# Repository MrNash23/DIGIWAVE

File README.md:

<h3 align="center">A pocket terminal for digital radio modes</h3>

<p align="center">
  Firmware for the <a href="https://lilygo.cc/products/t-lora-pager">LilyGo T-LoRa Pager</a>:
  FT8, FT4, CW, RTTY, NAVTEX, WEFAX and SSTV on a device that fits in a jacket pocket,
  and a scanner that tells them apart.
</p>

## What it does

DIGIWAVE listens to the audio of a radio, decodes what it hears and shows it on
the pager's display. In the modes that can transmit it also generates the audio
and keys the radio. No computer is involved.

<table>
  <tr>
    <td align="center"><br><b>FT8</b></td>
    <td align="center"><br><b>FT4</b></td>
    <td align="center"><br><b>CW</b></td>
    <td align="center"><br><b>RTTY</b></td>
    <td align="center"><br><b>NAVTEX</b></td>
    <td align="center"><br><b>WEFAX</b></td>
    <td align="center"><br><b>SSTV</b></td>
    <td align="center"><br><b>SCAN</b></td>
  </tr>
</table>

| Mode | Receive | Transmit |
| --- | --- | --- |
| FT8, FT4 | yes, with locator and country of each station | yes, with automatic QSO sequence and ADIF log |
| CW | yes, in a 100 Hz window that is moved with the wheel | yes, from the keyboard |
| RTTY (45.45 / 50 baud) | yes | yes |
| NAVTEX | yes | - |
| WEFAX (120 LPM) | yes, saved as BMP on the SD card | - |
| SSTV (Martin 1/2, Scottie 1/2, Robot 36, PD 120/180) | yes, in colour, saved as BMP on the SD card | - |
| Mode scanner (experimental) | names the mode of a signal: FT8, FT4, CW, RTTY, NAVTEX, PSK31/63, SSTV, WEFAX | - |

### Features

- **Mode scanner** (experimental): the SCAN tile listens to the strongest
  signal, or to the one picked with the wheel, and names its mode from its
  width, tones, symbol rate and length of transmission, with the measured
  shift, baud rate or speed. Enter opens the mode that decodes it and takes the
  tones over, for instance mark, shift and speed of an RTTY station
- **Waterfall** under the decodes in FT8, FT4, CW, RTTY and NAVTEX
- **Full FT8/FT4 contacts**: call CQ or answer a station with one press; the
  sequence runs by itself and the contact is written to an ADIF logbook on the SD card
- **Worked before**: stations already in the logbook of the device are greyed
  out in the list, on this band or only on another one
- **CQ with an addition** (POTA, SOTA, DX, QRP ...), **distance** to every
  station heard, and **figures over the logbook**: QSOs per band and mode,
  countries, farthest contact
- **Weather by RTTY**: the frequencies of the German weather service DWD are in
  the RTTY list; choosing one sets speed and shift
- **CB (11 m) operation** for FT8 and FT4: CB callsigns such as `26AT016`, the
  message sequence of WSJT-CB and the country list by division number
- **The own contact at a glance**: what is sent appears in the list with what
  is heard, and while calling or working a station the list shows just that
  contact (key V switches between it and everything heard)
- **A free spot to transmit**: the spectrum of the last half minute shows
  where the band is quiet; key G moves the TX frequency there, key F tunes it
  with the wheel on the waterfall, and key E chooses the first or the second
  slots for calling CQ
- **Voice announcements** (optional): a new station calling CQ, a station
  calling you, a QSO started and logged, spoken through the pager's speaker
- **Band and frequency for the logbook**: the radio is tuned by hand, so key B
  in FT8 and FT4 opens the list of the usual frequencies per band (or takes a
  typed one). FT8, FT4 and CB operation each remember their own
- **Exact time from GPS** with the pulse-per-second signal. Without reception
  the phone page sets the clock from the phone's time, measured like NTP, and
  the real-time clock keeps it in between
- **Locator from GPS**, or entered by hand
- **Phone page over Wi-Fi** (switched on and off in the setup): the pager opens its own access point and serves a
  page with the decodes, the main controls, received WEFAX pictures and the
  logbook download. In the logbook, key Q shows QR codes that join the Wi-Fi
  and fetch the ADIF file
- **Home network**: set up from the phone without typing on the pager. Setup >
  Home Wi-Fi shows a code that joins the pager and one that opens a page
  listing the networks in reach, where the password is pasted. The pager then
  joins that network besides its own access point whenever its Wi-Fi is on,
  and answers there as `digiwave.local`, so a logging program at home can take
  the logbook over and send its own QSOs back (see
  [Logbook over the home network](#logbook-over-the-home-network)). With Wi-Fi
  off, the home network is left alone too
- **Worked from home**: QSOs a logging program puts on the card mark those
  stations as worked in the list of decodes, and key A in the logbook shows them
  together with the own QSOs, with their distance
- **Broadcast plans** of the German weather service DWD for WEFAX and RTTY: the
  menu names the next broadcast and the plan counts down to it; the plans can
  be edited on the phone page
- **Battery** charge in the corner of the screen, from the fuel gauge checked
  against the voltage curve of the cell
- **Power saving**: the display goes off after three minutes without input, and
  the device goes to sleep when nothing is received either. Pressing the wheel
  wakes it. "Switch off" is in the setup

## Hardware: connecting a radio

<table>
  <tr>
    <td width="40%"></td>
    <td width="30%"></td>
    <td width="30%"></td>
  </tr>
</table>

A small interface board plugs into the pager's 12-pin port. It carries its own
ES8311 audio codec with line in, line out and a PTT output, and connects to
the radio with one TRRS cable wired like the Digirig. The firmware uses it
whenever it is plugged in (Setup, "Audio"); receive and transmit levels are set
in the setup and with the two trimmers, which can be reached through the lid of
its 3D-printed case.

Schematic, KiCad project, Gerber files with parts list, 3D views and the STL
files of the case are in [`hardware`](hardware), described on its own
[page](hardware/README.md).

Without the board, audio goes through the built-in microphone and speaker of
the pager, so reception works held next to the speaker of any receiver.

## Status

Work in progress.

- The signal processing of all modes and the mode scanner are covered by 58
  host tests.
- On the device, FT8 reception has been checked against real signals; a slot is
  decoded in about 0.7 s.
- NAVTEX and SSTV have only been tested against generated signals; WEFAX has
  received real weather charts.
- The mode scanner is tested against generated signals down to 0 dB SNR and has
  named real RTTY of the German weather service (50 baud, 450 Hz shift).
- Transmitting works through the interface board: PTT keys the radio and FT8
  calls have gone out on the air.

## Installing

DIGIWAVE is installed as one application next to others (for example Meshtastic)
with the [Launcher](https://github.com/bmorcelli/Launcher) by bmorcelli: build
the firmware, copy `.pio/build/pager/firmware.bin` to the SD card and install it
from the Launcher. An update can also be written over USB straight into the
Launcher slot of DIGIWAVE (`ft8pag`), at the offset its partition table gives
it. The Launcher rewrites the table when applications are installed, so read it
first (`esptool.py read_flash 0x8000 0xc00 table.bin`); with the present table
the offset is 0x1a0000:

    esptool.py write_flash 0x1a0000 .pio/build/pager/firmware.bin

Do not use `pio run -t upload` on a pager with the Launcher: it writes
`partitions.csv`, the layout for running DIGIWAVE alone, together with its own
bootloader, and so removes the Launcher and the other applications.

## Building

PlatformIO with the pioarduino platform (Arduino-ESP32 3.3):

    pio run -e pager        # firmware
    pio test -e native      # host tests of the signal processing

Artwork in `DIGIWAVE_Firmware_Grafiken` is converted with `python3 tools/make_assets.py`,
the voice announcements are spoken by [Piper](https://github.com/OHF-Voice/piper1-gpl)
with `tools/make_voice.py` (setup in the script).

## Operating

The same everywhere:

| | |
| --- | --- |
| Wheel | select or tune: a tile, a station, the CW receive window, the RTTY tones |
| Wheel press | in the menu: open. In a mode: the list of its functions, with the keys that do the same directly |
| Enter | the main action of the mode: call the selected station, send the typed line, save the received picture |
| Backspace | one step back: typed text first, then the open list or page, then from the mode to the menu |
| Space + key | digits and symbols |

FT8 and FT4 keep a line with their keys at the bottom of the screen; the other
modes use the whole screen for text, spectrum or picture.

The scanner analyses every two seconds: the wheel picks a signal on the
waterfall, A goes back to the strongest, Enter opens the mode that decodes it.
A guess shows once two analyses agree. "Input too quiet" means next to no audio
arrives: check the cable and the level of the radio.

Every WEFAX line is kept in memory (half an hour of reception), so a picture
can be saved as a whole at any time, and is saved by itself when the station's
stop tone ends it. Saved pictures can be looked at on the pager
(WEFAX functions, "Saved pictures") and are shown, downloaded and deleted on
the phone page.

## Logbook over the home network

With a home network set up (Setup > Home Wi-Fi) and Wi-Fi on, the pager answers
at `http://digiwave.local`. A logging program on a computer in that network can
use three requests to keep its log and the pager's in step, in both directions:

| Request | |
| --- | --- |
| `GET /api/log` | `{"device":"DIGIWAVE", "call":"...", "qsos":12, "size":975, "station":14759, "stationqsos":92}`: QSOs and size in bytes of the pager's logbook, size of the station file and the QSOs in it; a size is `-1` while there is no such file |
| `GET /log.adi` | the pager's logbook as ADIF |
| `POST /api/station` | replaces the station file with the body (`Content-Type: text/plain`), which is written to the card as it arrives; answers `200` once it is in place |

**Taking the logbook over.** The pager only ever appends to its logbook and
never deletes from it, so it is enough to ask `/api/log` now and then and to
fetch `/log.adi` when `size` changed. Records may come again: match them on
your side, by call, date, time, band and mode. The file starts with a header
naming `DIGIWAVE` as `programid`, and every record carries `station_callsign`
and `my_gridsquare` of where it was worked, which is useful for portable
operation.

**Sending QSOs to the pager.** QSOs made elsewhere, at the home station for
instance, go into the station file. The pager marks these stations as worked in
the list of decodes and for the voice announcements, lists them in grey in the
logbook (key A) with their distance, leaves them out of the figures and never
returns them in `/log.adi`. The file is ADIF with these rules:

- one record to a line, ending in `<eor>`, lines up to 400 bytes
- oldest first: the pager keeps the newest 200 for its list
- fields read: `call` and `band` (for marking as worked), `gridsquare` and
  `my_gridsquare` (for the distance), `qso_date`, `time_on`, `mode`,
  `submode`, `rst_sent`, `rst_rcvd`
- at most 6000 records together with the pager's own logbook; the file is read
  at every start, so keep it smaller where you can. With more QSOs than that,
  send the newest of every call and band first
- send it only when it changed: compare `station` in `/api/log` with the size
  of what you sent last, which also catches another card in the pager

**Staying awake.** Each `/api/log` or `/log.adi` keeps the pager from going to
sleep for three minutes, so asking once a minute keeps it on while it is at
home. The display still goes off.

**Name and safety.** The pager announces its name over mDNS with an IPv4
address only. Resolve `digiwave.local` for IPv4: a lookup for any address
family can wait several seconds for an IPv6 answer that never comes (macOS
waits five). The interface has no password; everything in the home network can
reach it, the phone page with its transmit controls included.

## Layout of the repository

- `lib/ft8core` - hardware-independent decoders, encoders and QSO logic
- `lib/ft8_lib` - vendored [kgoba/ft8_lib](https://github.com/kgoba/ft8_lib) (MIT)
- `src` - firmware: audio and PTT interfaces, engine, user interface, web interface
- `test` - host tests and reference recordings from ft8_lib
- `hardware` - interface board (KiCad project, schematic, fabrication files) and printed case
- `PROJEKT.md` - description of the project in German

## Licence and credits

Copyright (C) 2026 Andres Leroi

DIGIWAVE is free software: you can redistribute it and/or modify it under the
terms of the GNU General Public License as published by the Free Software
Foundation, either version 3 of the License, or (at your option) any later
version. It comes without any warranty. The text is in [`LICENSE`](LICENSE).

The hardware in [`hardware`](hardware), interface board and case, is licensed
under the CERN Open Hardware Licence Version 2 - Strongly Reciprocal
(CERN-OHL-S-2.0), text in [`hardware/LICENSE`](hardware/LICENSE).

It stands on the work of others:

- **FT8 and FT4** are protocols by Joe Taylor K1JT and Steve Franke K9AN;
  coding and decoding come from [ft8_lib](https://github.com/kgoba/ft8_lib) by
  Kārlis Goba (MIT)
- **CB operation** follows [WSJT-CB](https://github.com/vash909/WSJT-CB), from
  which the list of 11 m divisions is taken (GPL-3.0)
- **The voice announcements** are spoken by Piper (GPL-3.0) with the voice
  ljspeech, trained on the public-domain LJ Speech dataset
- **The device** is driven through [LilyGoLib](https://github.com/Xinyuan-LilyGO/LilyGoLib)
  (MIT), the display through [LVGL](https://github.com/lvgl/lvgl) (MIT) with
  the Montserrat typeface (SIL Open Font License)
- **The platform** is the Arduino core for ESP32 (LGPL-2.1) on ESP-IDF (Apache-2.0)

The complete list with versions, authors and licences is in
[`THIRD-PARTY-NOTICES.md`](THIRD-PARTY-NOTICES.md). The same credits are shown
on the device under Setup, "About DIGIWAVE".

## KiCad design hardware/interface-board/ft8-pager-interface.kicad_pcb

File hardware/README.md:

<h3 align="center">DIGIWAVE interface board</h3>

<p align="center">
  Line in, line out and PTT for the LilyGo T-LoRa Pager, in a small case that
  plugs into the pager's 12-pin port. One TRRS cable goes to the radio.
</p>

## What it does

The pager has no audio connection for a radio. The board adds one: its own
ES8311 audio codec, clocked and fed over I²S from the 12-pin port, a 3.5 mm
TRRS jack for the radio and an open-collector PTT output. DIGIWAVE finds the
board at start-up and uses it instead of the built-in microphone and speaker
(Setup, "Audio").

<table>
  <tr>
    <td width="50%"></td>
    <td width="50%"></td>
  </tr>
  <tr>
    <td align="center">The assembled board</td>
    <td align="center">The same board in KiCad's 3D view</td>
  </tr>
</table>

- **Audio codec** ES8311 at I²C address 0x19 (the pager's own codec is at 0x18).
  It has no MCLK and derives its clock from BCLK.
- **One data line for both directions**: the port offers a single pin for audio
  data, so an analogue switch (SN74LVC1G3157) connects it to the codec's ADC
  while receiving and to its DAC while the PTT line is set
- **Receive**: tip of the jack → protection → trimmer RV1 → codec input
- **Transmit**: codec output → trimmer RV2 → 470 Ω → ring of the jack
- **PTT**: MMBT3904 as open collector, protected up to 15 V
- **Protection** on every line to the radio with TVS diodes
- **Supply** from the pager's 3.3 V; analogue supply through a ferrite bead,
  analogue and digital ground joined at one point

## Schematic

<p align="center">
  
</p>

The schematic as [PDF](interface-board/schematic.pdf); the KiCad 10 project is in
[`interface-board`](interface-board).

## Connections

### Pager port J3 (2 × 6, 2.54 mm)

| Pin | Signal | Use on the board |
| --- | --- | --- |
| 1 | GND | ground |
| 2 | 3V3 | supply |
| 3 | GPIO43 | I²S BCLK |
| 4 | GPIO44 | I²S LRCK |
| 8 | GPIO9 | I²S data, both directions |
| 9 | SDA | I²C to the codec |
| 10 | XL9555 P11 | PTT_CTRL: keys the radio and switches the data line to the DAC |
| 11 | SCL | I²C to the codec |
| 5, 6, 7, 12 | SPI, VBUS | not used |

### Radio jack J2 (3.5 mm TRRS)

The jack is wired like the [Digirig](https://digirig.net/), so the cables made
for it fit:

| Contact | Signal |
| --- | --- |
| Tip | audio from the radio (RX) |
| Ring 1 | audio to the radio (TX) |
| Ring 2 | PTT |
| Sleeve | ground |

### Jumpers, trimmers and test points

| Part | Purpose |
| --- | --- |
| JP2, JP3 | Ring swap. As delivered (1–2 bridged), ring 1 carries TX audio and ring 2 the PTT. Bridging 2–3 on both swaps them |
| JP1 | open: TX audio through a capacitor. Bridged: DC-coupled, for radios that need it |
| RV1 | receive level |
| RV2 | transmit level. If PTT keys the radio but nothing is heard, turn this up first |
| TP1–TP15 | BCLK, LRCK, DATA, ASDOUT, DSDIN, MCLK, SDA, SCL, 3V3, 3V3A, GND, TIP_RX, RING1, RING2, PTT_CTRL |

## Case

<table>
  <tr>
    <td width="50%"></td>
    <td width="50%"></td>
  </tr>
  <tr>
    <td align="center">Base, board and lid</td>
    <td align="center">From below: the header goes into the pager</td>
  </tr>
</table>

Two printed parts, 45.4 × 30.4 mm, 10.5 mm high when closed. The 12-pin
header comes out through the window in the base and plugs straight into the
pager. The lid has openings over both trimmers, so the levels can be set with
the case closed. The jack is reached from the side.

GitHub shows STL files as a 3D model that can be turned with the mouse:

- [`case/case-base.stl`](case/case-base.stl), base
- [`case/case-lid.stl`](case/case-lid.stl), lid
- [`interface-board/interface-board.stl`](interface-board/interface-board.stl), the assembled board

## Building one

The board was made and assembled by JLCPCB. Everything needed for the order is
in [`interface-board/fabrication`](interface-board/fabrication):

| File | Content |
| --- | --- |
| `gerber.zip` | Gerber and drill files, two layers |
| `bom-jlcpcb.csv` | parts list with LCSC part numbers |
| `cpl-jlcpcb.csv` | placement file |

The 12-pin header is fitted by hand, pointing down out of the board. The board as a whole is also
available as [STEP](interface-board/interface-board.step) for designing other
cases.

## Files

| Path | Content |
| --- | --- |
| `interface-board/ft8-pager-interface.kicad_pro`, `.kicad_sch`, `.kicad_pcb` | KiCad 10 project |
| `interface-board/lib/ft8_pager.kicad_sym` | symbols of ES8311, analogue switch and jack |
| `interface-board/schematic.pdf` | schematic |
| `interface-board/interface-board.step`, `.stl` | 3D model of the assembled board |
| `interface-board/fabrication` | Gerber files, parts list and placement for JLCPCB |
| `case/case-base.stl`, `case/case-lid.stl` | case for 3D printing |

The 3D model of the jack (PJ-320D, LCSC C22459515) comes from the EasyEDA
library and is not in the repository; the KiCad project shows the board
without it until `lib/3d/PJ-320D.step` is added. The exported STEP and STL
include it.

The firmware side is in `src/hal/audio_es8311.cpp` (codec and data line) and
`src/hal/ptt_xl9555.cpp` (PTT).

## Licence

Copyright (C) 2026 Andres Leroi.

The hardware in this directory, the interface board and the case, is licensed
under the CERN Open Hardware Licence Version 2 - Strongly Reciprocal
(CERN-OHL-S-2.0), text in [`LICENSE`](LICENSE). It may be used, studied,
changed, built and sold; whoever passes on the design or a product made from
it has to make the source of the design, with any changes, available under the
same licence.

Source location: https://github.com/MrNash23/DIGIWAVE/tree/main/hardware

The firmware in the rest of the repository stays under the GNU General Public
License, version 3 or later. The footprints and 3D models of the KiCad
libraries are used under their licence (CC-BY-SA 4.0 with an exception that
leaves designs made with them free).

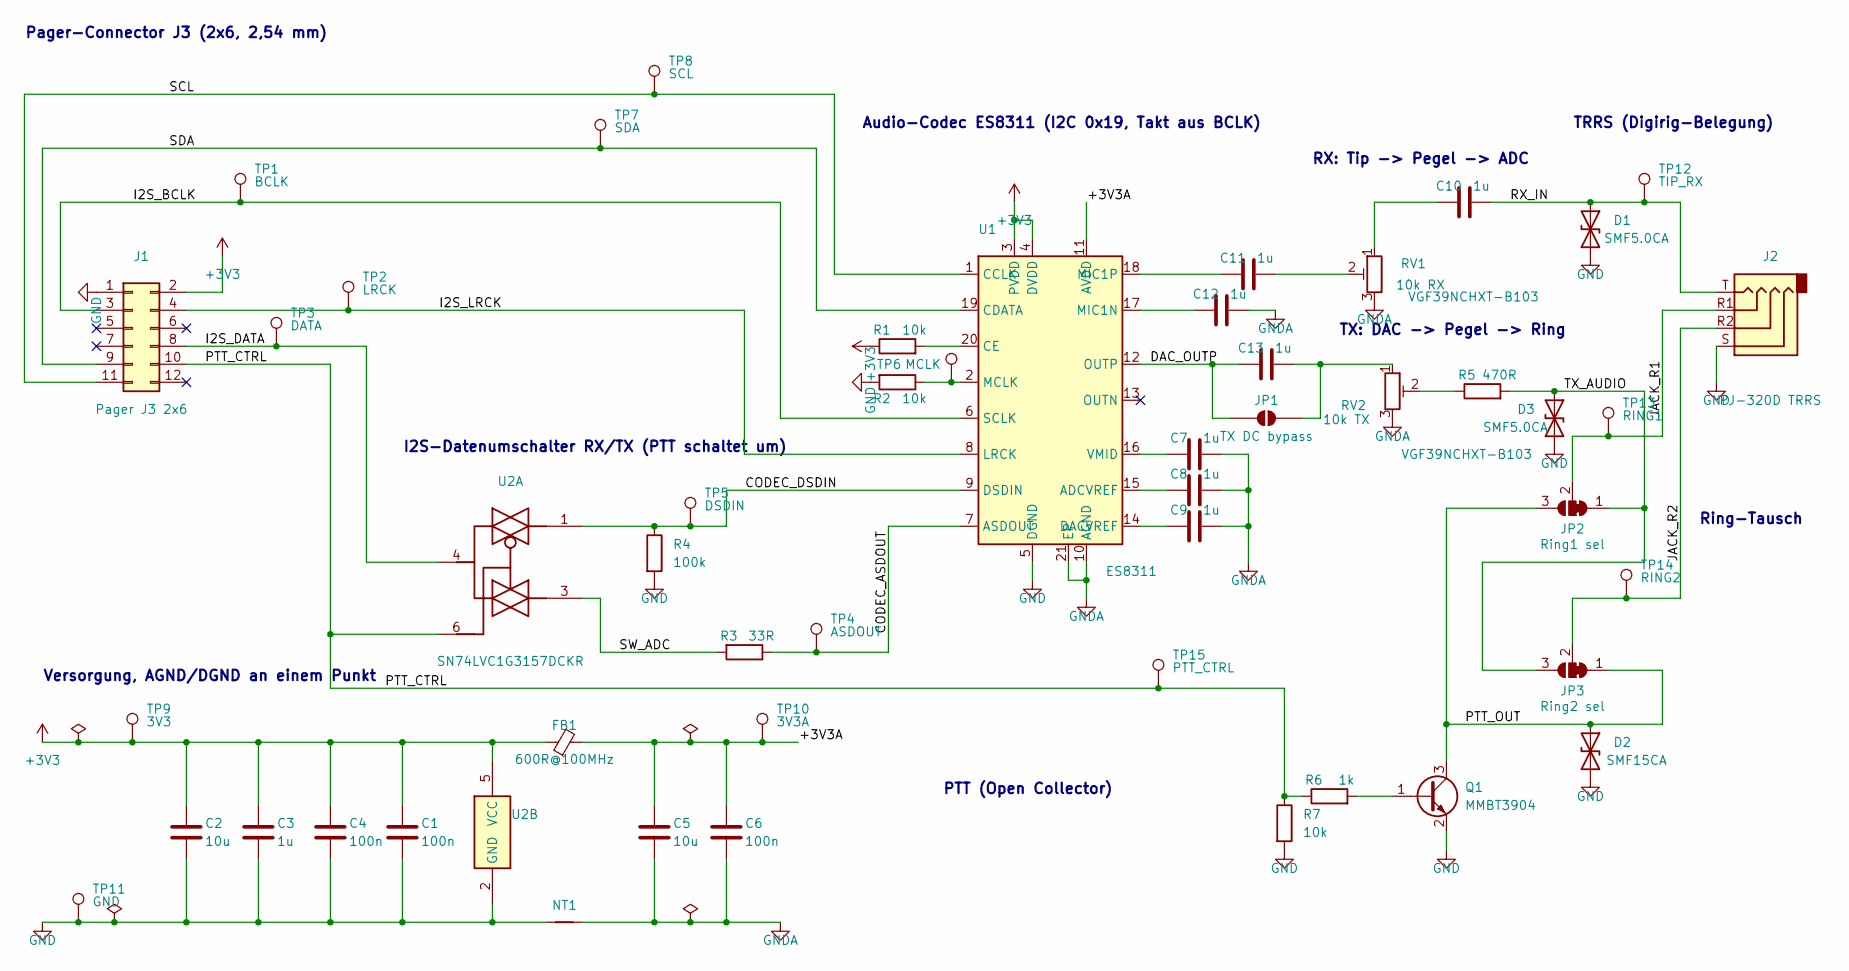
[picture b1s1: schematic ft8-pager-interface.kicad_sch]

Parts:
C1, C4, C6: 100n; C_0402_1005Metric
C2, C5: 10u; C_0603_1608Metric
C3, C7, C8, C9, C10, C11, C12, C13: 1u; C_0402_1005Metric
D1, D3: SMF5.0CA; D_SOD-123F
D2: SMF15CA; D_SOD-123F
FB1: 600R@100MHz; L_0603_1608Metric
J1: Pager J3 2x6; PinHeader_2x06_P2.54mm_Vertical
J2: PJ-320D TRRS; Jack_3.5mm_PJ320D_Horizontal
JP1: TX DC bypass; SolderJumper-2_P1.3mm_Open_RoundedPad1.0x1.5mm
JP2: Ring1 sel; SolderJumper-3_P1.3mm_Bridged12_RoundedPad1.0x1.5mm
JP3: Ring2 sel; SolderJumper-3_P1.3mm_Bridged12_RoundedPad1.0x1.5mm
NT1: AGND-DGND; NetTie-2_SMD_Pad0.5mm
Q1: MMBT3904; SOT-23
R1, R2, R7: 10k; R_0402_1005Metric
R3: 33R; R_0402_1005Metric
R4: 100k; R_0402_1005Metric
R5: 470R; R_0402_1005Metric
R6: 1k; R_0402_1005Metric
RV1: 10k RX; Potentiometer_Bourns_TC33X_Vertical; MPN VGF39NCHXT-B103; LCSC C22461454
RV2: 10k TX; Potentiometer_Bourns_TC33X_Vertical; MPN VGF39NCHXT-B103; LCSC C22461454
TP1: BCLK; TestPoint_Pad_D1.0mm
TP2: LRCK; TestPoint_Pad_D1.0mm
TP3: DATA; TestPoint_Pad_D1.0mm
TP4: ASDOUT; TestPoint_Pad_D1.0mm
TP5: DSDIN; TestPoint_Pad_D1.0mm
TP6: MCLK; TestPoint_Pad_D1.0mm
TP7: SDA; TestPoint_Pad_D1.0mm
TP8: SCL; TestPoint_Pad_D1.0mm
TP9: 3V3; TestPoint_Pad_D1.0mm
TP10: 3V3A; TestPoint_Pad_D1.0mm
TP11: GND; TestPoint_Pad_D1.0mm
TP12: TIP_RX; TestPoint_Pad_D1.0mm
TP13: RING1; TestPoint_Pad_D1.0mm
TP14: RING2; TestPoint_Pad_D1.0mm
TP15: PTT_CTRL; TestPoint_Pad_D1.0mm
U1: ES8311; QFN-20-1EP_3x3mm_P0.4mm_EP1.65x1.65mm
U2: SN74LVC1G3157DCKR; SOT-363_SC-70-6

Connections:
+3V3: C1.1, C2.1, C3.1, C4.1, FB1.1, J1.2, R1.1, TP9.1, U1.3 (PVDD), U1.4 (DVDD), U2.5 (VCC)
/+3V3A: C5.1, C6.1, FB1.2, TP10.1, U1.11 (AVDD)
/CODEC_ASDOUT: R3.1, TP4.1, U1.7 (ASDOUT)
/CODEC_DSDIN: R4.1, TP5.1, U1.9 (DSDIN), U2.1
/DAC_OUTP: C13.1, JP1.1 (A), U1.12 (OUTP)
/I2S_BCLK: J1.3, TP1.1, U1.6 (SCLK)
/I2S_DATA: J1.8, TP3.1, U2.4
/I2S_LRCK: J1.4, TP2.1, U1.8 (LRCK)
/JACK_R1: J2.R1, JP2.2 (C), TP13.1
/JACK_R2: J2.R2, JP3.2 (C), TP14.1
/PTT_CTRL: J1.10, R6.1, R7.1, TP15.1, U2.6
/PTT_OUT: D2.1 (A1), JP2.3 (B), JP3.1 (A), Q1.3 (C)
/RX_IN: C10.1, D1.1 (A1), J2.T, TP12.1
/SCL: J1.11, TP8.1, U1.1 (CCLK)
/SDA: J1.9, TP7.1, U1.19 (CDATA)
/SW_ADC: R3.2, U2.3
/TX_AUDIO: D3.1 (A1), JP2.1 (A), JP3.3 (B), R5.2
GND: C1.2, C2.2, C3.2, C4.2, D1.2 (A2), D2.2 (A2), D3.2 (A2), J1.1, J2.S, NT1.1, Q1.2 (E), R2.2, R4.2, R7.2, TP11.1, U1.5 (DGND), U2.2 (GND)
GNDA: C5.2, C6.2, C7.2, C8.2, C9.2, C12.2, NT1.2, RV1.3, RV2.3, U1.10 (AGND), U1.21 (EP)
unnamed: C10.2, RV1.1
unnamed: C11.1, RV1.2
unnamed: C13.2, JP1.2 (B), RV2.1
unnamed: Q1.1 (B), R6.2
unnamed: R5.1, RV2.2
unnamed: C8.1, U1.15 (ADCVREF)
unnamed: R1.2, U1.20 (CE)
unnamed: C9.1, U1.14 (DACVREF)
unnamed: R2.1, TP6.1, U1.2 (MCLK)
unnamed: C12.1, U1.17 (MIC1N)
unnamed: C11.2, U1.18 (MIC1P)
unnamed: C7.1, U1.16 (VMID)

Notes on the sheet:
Pager-Connector J3 (2x6, 2,54 mm)
I2S-Datenumschalter RX/TX (PTT schaltet um)
Audio-Codec ES8311 (I2C 0x19, Takt aus BCLK)
RX: Tip -> Pegel -> ADC
TX: DAC -> Pegel -> Ring
Ring-Tausch
PTT (Open Collector)
Versorgung, AGND/DGND an einem Punkt
TRRS (Digirig-Belegung)

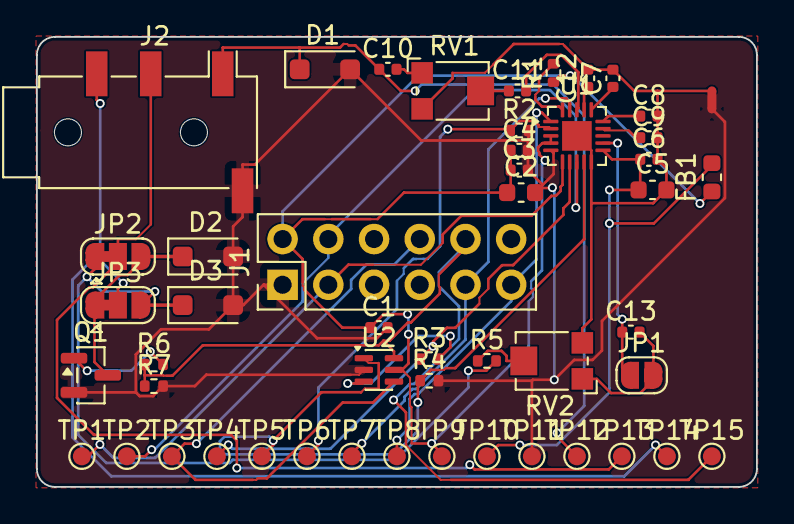
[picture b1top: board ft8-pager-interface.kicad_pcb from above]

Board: 2 copper layers, 40.0 x 25.0 mm, 50 parts (0 on the bottom side), 31 nets.

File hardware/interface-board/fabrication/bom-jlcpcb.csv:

Comment,Designator,Footprint,LCSC Part #
100n,"C1,C4,C6",C_0402_1005Metric,C1525
10u,"C2,C5",C_0603_1608Metric,C19702
1u,"C3,C7,C8,C9,C10,C11,C12,C13",C_0402_1005Metric,C52923
SMF5.0CA,"D1,D3",D_SOD-123F,C19077498
SMF15CA,D2,D_SOD-123F,C19077510
600R@100MHz,FB1,L_0603_1608Metric,C1002
PJ-320D TRRS,J2,Jack_3.5mm_PJ320D_Horizontal,C22459515
MMBT3904,Q1,SOT-23,C7420353
10k,"R1,R2,R7",R_0402_1005Metric,C25744
33R,R3,R_0402_1005Metric,C25105
100k,R4,R_0402_1005Metric,C25741
470R,R5,R_0402_1005Metric,C25117
1k,R6,R_0402_1005Metric,C11702
10k RX (VGF39NCHXT-B103),RV1,Potentiometer_Bourns_TC33X_Vertical,C22461454
10k TX (VGF39NCHXT-B103),RV2,Potentiometer_Bourns_TC33X_Vertical,C22461454
ES8311,U1,QFN-20-1EP_3x3mm_P0.4mm_EP1.65x1.65mm,C962342
SN74LVC1G3157DCKR,U2,SOT-363_SC-70-6,C41431793
